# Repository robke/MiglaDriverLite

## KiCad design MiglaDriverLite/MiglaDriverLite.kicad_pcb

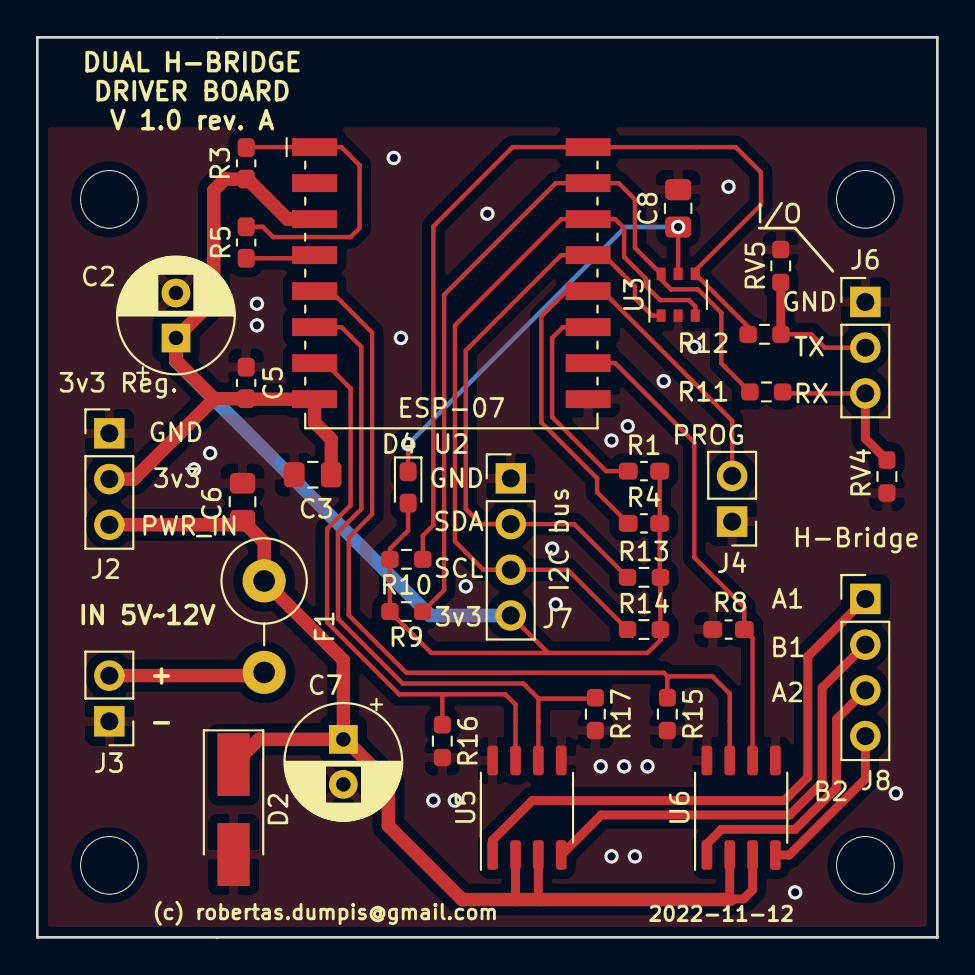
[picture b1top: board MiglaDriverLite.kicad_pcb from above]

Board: 2 copper layers, 50.0 x 50.0 mm, 39 parts (0 on the bottom side), 23 nets.

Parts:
C2, C7: 470uF; CP_Radial_D6.3mm_P2.50mm
C3, C6: 10uF; C_0805_2012Metric_Pad1.15x1.40mm_HandSolder
C5: 1uF; C_0603_1608Metric_Pad1.05x0.95mm_HandSolder
C8: 10uF; C_0805_2012Metric_Pad1.18x1.45mm_HandSolder
D2: SMAJ5.0A; D_SMA_Handsoldering
D4: 1N4148WT; D_0603_1608Metric_Pad1.05x0.95mm_HandSolder
F1: 2000mA; R_Axial_DIN0414_L11.9mm_D4.5mm_P5.08mm_Vertical
J2: 3V3_VR; PinHeader_1x03_P2.54mm_Vertical
J3: PWR_IN; PinHeader_1x02_P2.54mm_Vertical
J4: PROG; PinHeader_1x02_P2.54mm_Vertical
J6: I/O; PinHeader_1x03_P2.54mm_Vertical
J7: I2C; PinHeader_1x04_P2.54mm_Vertical
J8: H-Bridge; PinHeader_1x04_P2.54mm_Vertical
MOUNT: MountingHole_3.2mm_M3_DIN965
MOUNT#2, MOUNT#3, MOUNT#4: MountingHole_3.2mm_M3_DIN965
R1, R4: 4k6; R_0603_1608Metric_Pad1.05x0.95mm_HandSolder
R3: 10k; R_0603_1608Metric_Pad1.05x0.95mm_HandSolder
R5: 1k; R_0603_1608Metric_Pad1.05x0.95mm_HandSolder
R8: 4.6k; R_0603_1608Metric_Pad1.05x0.95mm_HandSolder
R9, R10, R13, R14: 4k6; R_0603_1608Metric_Pad0.98x0.95mm_HandSolder
R11, R12: 220; R_0603_1608Metric_Pad0.98x0.95mm_HandSolder
R15, R16, R17: 4.6k; R_0603_1608Metric_Pad0.98x0.95mm_HandSolder
RV4, RV5: Varistor; R_0603_1608Metric_Pad0.98x0.95mm_HandSolder
U2: ESP-07
U3: PRTR5V0U4D; TSOP-6_1.65x3.05mm_P0.95mm
U5, U6: L9110; SOP-8_3.9x4.9mm_P1.27mm

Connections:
+3V3: C2.1, C3.1, C5.1, D4.2, J2.2, J7.4, R1.2, R3.1, R4.2, R9.2, R10.2, R13.2, R14.2, U2.3, U2.8
+5V: C6.1, C7.1, D2.1, F1.1, J2.3, U5.2, U5.3, U6.2, U6.3
/GPIO0: J4.2, R4.1, U2.12
/GPIO4: J7.2, R13.1, U2.13, U3.1
/GPIO5: J7.3, R14.1, U2.14, U3.3
/GPIO12: R17.1, U2.6, U5.6
/GPIO13: R16.1, U2.7, U5.7
/GPIO14: R15.1, U2.5, U6.7
/GPIO15: R8.1, U2.10, U6.6
/RXD: R9.1, R11.1, U2.15, U3.6
/TXD: R10.1, R12.1, U2.16, U3.4
GND: C2.2, C3.2, C5.2, C6.2, C7.2, C8.2, D2.2, J2.1, J3.1, J4.1, J6.1, J7.1, R8.2, R15.2, R16.2, R17.2, RV4.1, RV5.1, U2.9, U3.2, U5.5, U5.8, U6.5, U6.8
unnamed: C8.1, D4.1, U3.5
unnamed: F1.2, J3.2
unnamed: J6.2, R12.2, RV5.2
unnamed: J6.3, R11.2, RV4.2
unnamed: J8.1, U5.1
unnamed: J8.2, U5.4
unnamed: J8.3, U6.1
unnamed: J8.4, U6.4
unnamed: R1.1, U2.11
unnamed: R3.2, R5.1, U2.1
unnamed: R5.2, U2.4

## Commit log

2023-06-23 Initial version 1.0 rev. A
2023-12-18 Pridėta
